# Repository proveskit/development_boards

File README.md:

# development_boards
Miscellaneous dev boards to test the components of the PROVES Kit on a smaller scale. 

## flat_sat_dev_board
This board is intended to be a "FlatSat" stand in for all of the core hardware of the PROVES Kit! By putting all of the microcontrollers, sensors, and communications hardware on one convenient board you can carry it around with you where ever you'd like!

Find a link to the documentation for that [here](https://docs.proveskit.space/en/latest/core_documentation/hardware/flatsat_dev_board/)! 

## Camera_board_v2
This board is currently being developed for the Irvington High School Girls in STEM Club team, who are looking to fly a camera on Pleiades - Orpheus. 

## Mux_driver_board_v1
This board is a breakout hosting both the TCA I2C Multiplexer and an I2C based LED driver. It is intended to be mounted as a daughter card on another PCB and used to provide access to additional protected I2C buses. 

## FC_Advanced_Carrier 
This is the initial design for a board that is able to accept an NVIDIA Jetson Nano SoM.

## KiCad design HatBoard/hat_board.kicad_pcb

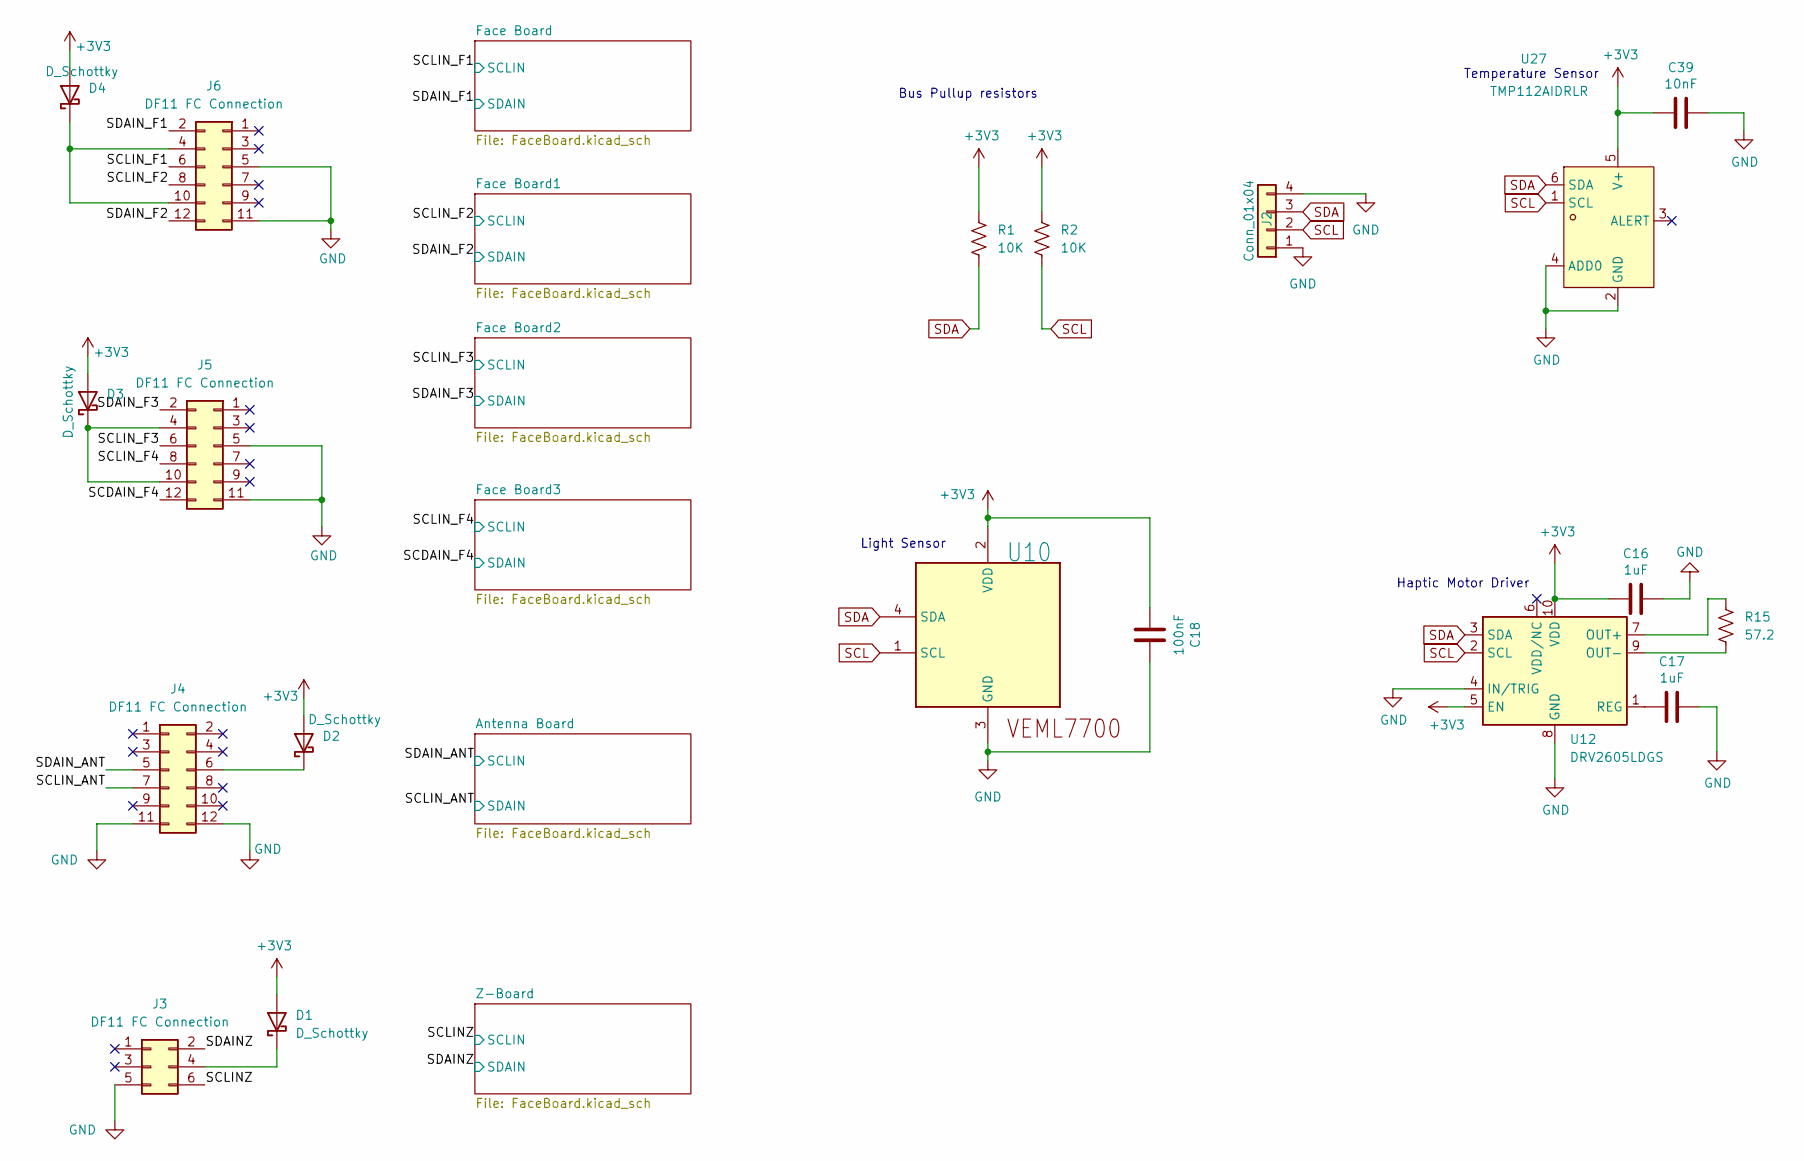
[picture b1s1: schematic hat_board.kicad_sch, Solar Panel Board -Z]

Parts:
C16, C17: 1uF; C_0805_2012Metric
C18: 100nF; C_0402_1005Metric
C39: 10nF; C_0402_1005Metric
D1, D2, D3, D4: D_Schottky; POWERDI-123_L2.8-W1.8-LS3.7-RD
J2: Conn_01x04; PinHeader_1x04_P2.00mm_Vertical
J3, J4, J5, J6: DF11 FC Connection; CONN-TH_DF11-12DS-2DSA-05
R1, R2: 10K; R_0603_1608Metric
R15: 57.2; R_0603_1608Metric
U10: VEML7700; SENSOR-SMD_EML7700-TT
U12: DRV2605LDGS; VSSOP-10_3x3mm_P0.5mm
U27: TMP112AIDRLR; SOT-563_L1.6-W1.2-P0.50-LS1.6-BR; LCSC Part C28927

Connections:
+3V3: C16.1, C18.1, C39.1, D1.2 (A), D2.2 (A), D3.2 (A), D4.2 (A), R1.2, R2.2, U10.2 (VDD), U12.5 (EN), U12.10 (VDD), U27.5 (V+); also elsewhere on the board
/SCDAIN_F4: J5.12; also elsewhere on the board
/SCLINZ: J3.6; also elsewhere on the board
/SCLIN_ANT: J4.7; also elsewhere on the board
/SCLIN_F1: J6.6; also elsewhere on the board
/SCLIN_F2: J6.8; also elsewhere on the board
/SCLIN_F3: J5.6; also elsewhere on the board
/SCLIN_F4: J5.8; also elsewhere on the board
/SDAINZ: J3.2; also elsewhere on the board
/SDAIN_ANT: J4.5; also elsewhere on the board
/SDAIN_F1: J6.2; also elsewhere on the board
/SDAIN_F2: J6.12; also elsewhere on the board
/SDAIN_F3: J5.2; also elsewhere on the board
GND: C16.2, C17.2, C18.2, C39.2, J2.1, J2.4, J3.5, J4.11, J4.12, J5.5, J5.11, J6.5, J6.11, U10.3 (GND), U12.4 (IN/TRIG), U12.8 (GND), U27.2 (GND), U27.4 (ADD0); also elsewhere on the board
unnamed: D1.1 (K), J3.4
unnamed: D2.1 (K), J4.6
unnamed: D3.1 (K), J5.4, J5.10
unnamed: D4.1 (K), J6.4, J6.10
unnamed: R15.1, U12.7 (OUT+)
unnamed: R15.2, U12.9 (OUT-)
unnamed: C17.1, U12.1 (REG)
SCL: J2.2, R2.1, U10.1 (SCL), U12.2 (SCL), U27.1 (SCL); also elsewhere on the board
SDA: J2.3, R1.1, U10.4 (SDA), U12.3 (SDA), U27.6 (SDA); also elsewhere on the board

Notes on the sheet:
Bus Pullup resistors
Temperature Sensor
Haptic Motor Driver
Light Sensor

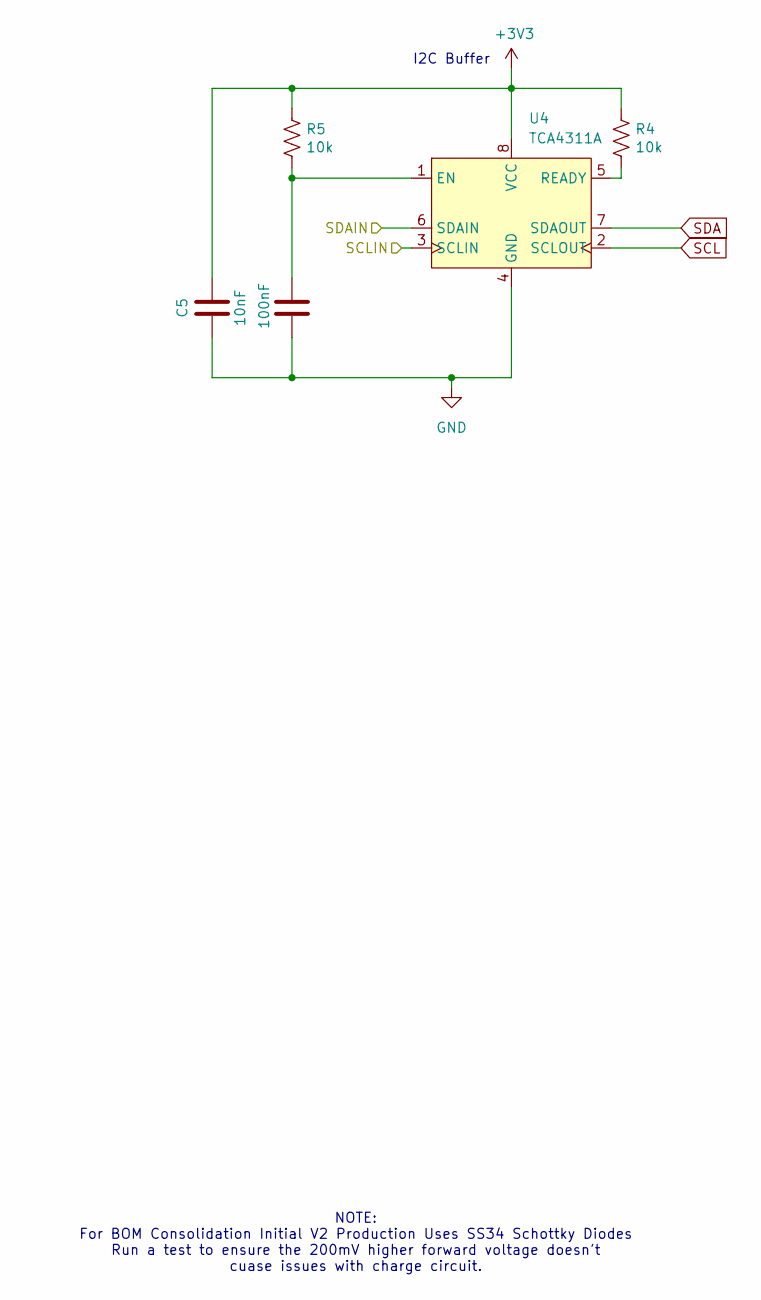
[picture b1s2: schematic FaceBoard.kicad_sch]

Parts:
C4: 100nF; C_0402_1005Metric
C5: 10nF; C_0805_2012Metric
R4, R5: 10k; R_0603_1608Metric
U4: TCA4311A; VSSOP-8_3x3mm_P0.65mm

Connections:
+3V3: C5.1, R4.1, R5.1, U4.8 (VCC); also elsewhere on the board
/SCLIN_F1: U4.3 (SCLIN); also elsewhere on the board
/SDAIN_F1: U4.6 (SDAIN); also elsewhere on the board
GND: C4.2, C5.2, U4.4 (GND); also elsewhere on the board
unnamed: C4.1, R5.2, U4.1 (EN)
unnamed: R4.2, U4.5 (READY)
SCL: U4.2 (SCLOUT); also elsewhere on the board
SDA: U4.7 (SDAOUT); also elsewhere on the board

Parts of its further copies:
C7, C13, C19, C25, C31: 10nF; C_0805_2012Metric
C8, C14, C20, C26, C32: 100nF; C_0402_1005Metric
R6, R7, R11, R12, R16, R17, R21, R22, R26, R27: 10k; R_0603_1608Metric
U5, U9, U13, U17, U21: TCA4311A; VSSOP-8_3x3mm_P0.65mm

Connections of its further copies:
+3V3: C7.1, C13.1, C19.1, C25.1, C31.1, R6.1, R7.1, R11.1, R12.1, R16.1, R17.1, R21.1, R22.1, R26.1, R27.1, U5.8 (VCC), U9.8 (VCC), U13.8 (VCC), U17.8 (VCC), U21.8 (VCC); also elsewhere on the board
/SCDAIN_F4: U13.6 (SDAIN); also elsewhere on the board
/SCLINZ: U17.3 (SCLIN); also elsewhere on the board
/SCLIN_ANT: U21.6 (SDAIN); also elsewhere on the board
/SCLIN_F2: U5.3 (SCLIN); also elsewhere on the board
/SCLIN_F3: U9.3 (SCLIN); also elsewhere on the board
/SCLIN_F4: U13.3 (SCLIN); also elsewhere on the board
/SDAINZ: U17.6 (SDAIN); also elsewhere on the board
/SDAIN_ANT: U21.3 (SCLIN); also elsewhere on the board
/SDAIN_F2: U5.6 (SDAIN); also elsewhere on the board
/SDAIN_F3: U9.6 (SDAIN); also elsewhere on the board
GND: C7.2, C8.2, C13.2, C14.2, C19.2, C20.2, C25.2, C26.2, C31.2, C32.2, U5.4 (GND), U9.4 (GND), U13.4 (GND), U17.4 (GND), U21.4 (GND); also elsewhere on the board
unnamed: C8.1, R6.2, U5.1 (EN)
unnamed: R7.2, U5.5 (READY)
unnamed: C14.1, R11.2, U9.1 (EN)
unnamed: R12.2, U9.5 (READY)
unnamed: C20.1, R16.2, U13.1 (EN)
unnamed: R17.2, U13.5 (READY)
unnamed: C26.1, R21.2, U17.1 (EN)
unnamed: R22.2, U17.5 (READY)
unnamed: C32.1, R26.2, U21.1 (EN)
unnamed: R27.2, U21.5 (READY)
SCL: U5.2 (SCLOUT), U9.2 (SCLOUT), U13.2 (SCLOUT), U17.2 (SCLOUT), U21.2 (SCLOUT); also elsewhere on the board
SDA: U5.7 (SDAOUT), U9.7 (SDAOUT), U13.7 (SDAOUT), U17.7 (SDAOUT), U21.7 (SDAOUT); also elsewhere on the board

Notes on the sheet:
NOTE: For BOM Consolidation Initial V2 Production Uses SS34 Schottky Diodes Run a test to ensure the 200mV higher forward voltage doesn't cuase issues with charge circuit.
I2C Buffer

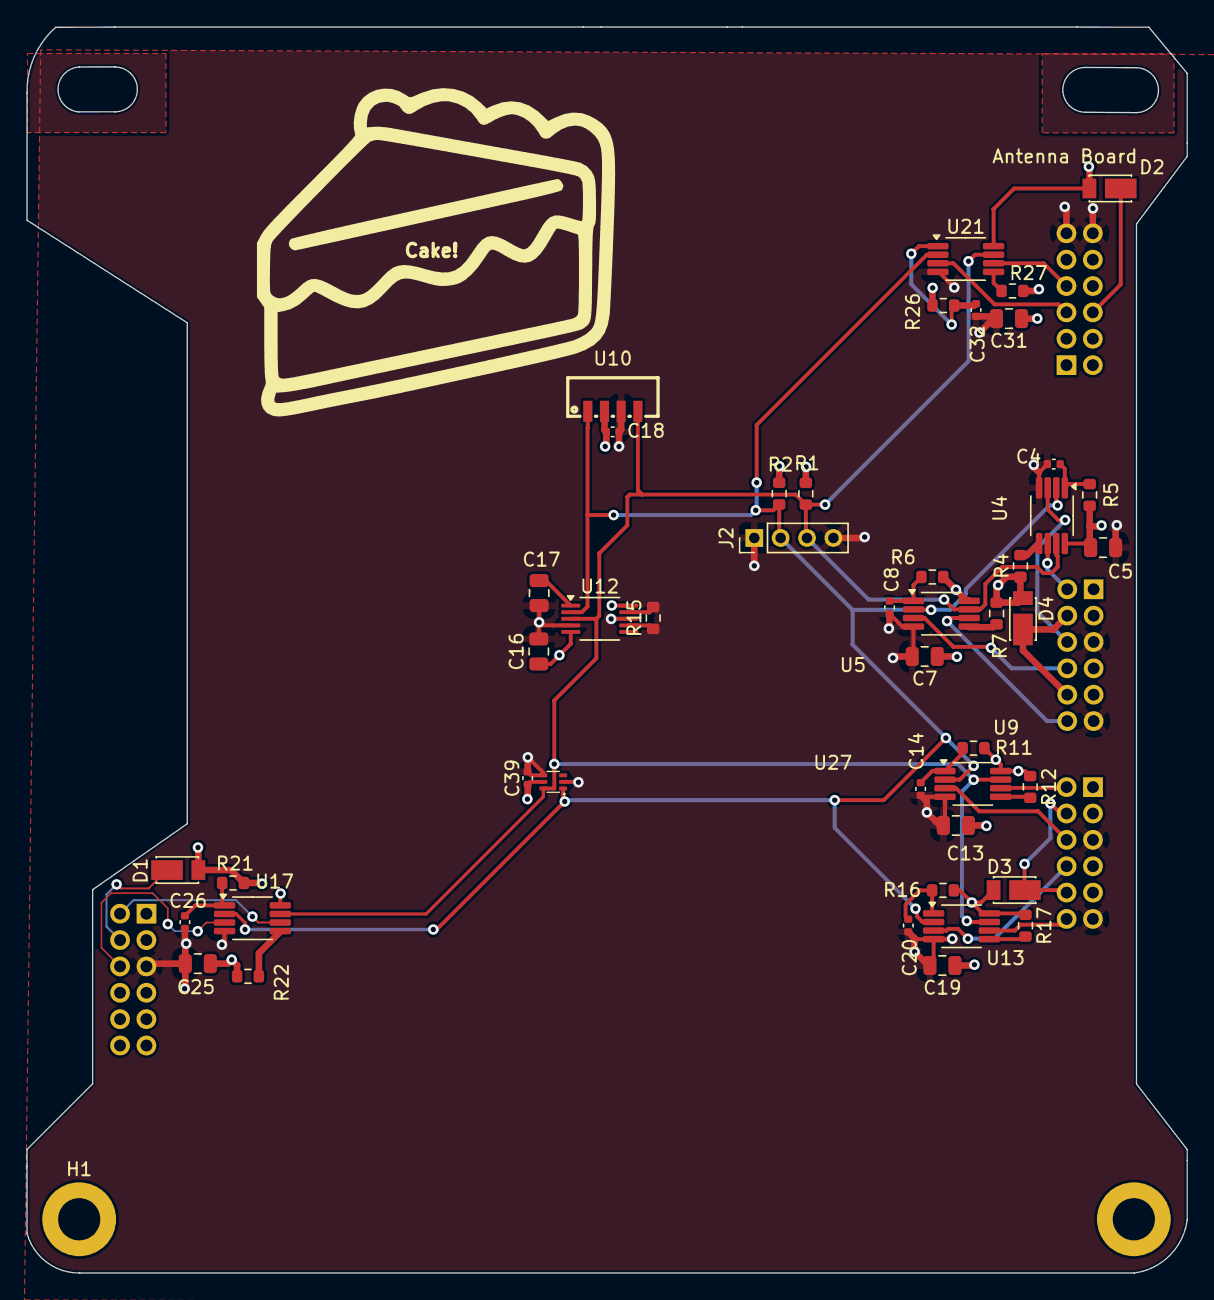
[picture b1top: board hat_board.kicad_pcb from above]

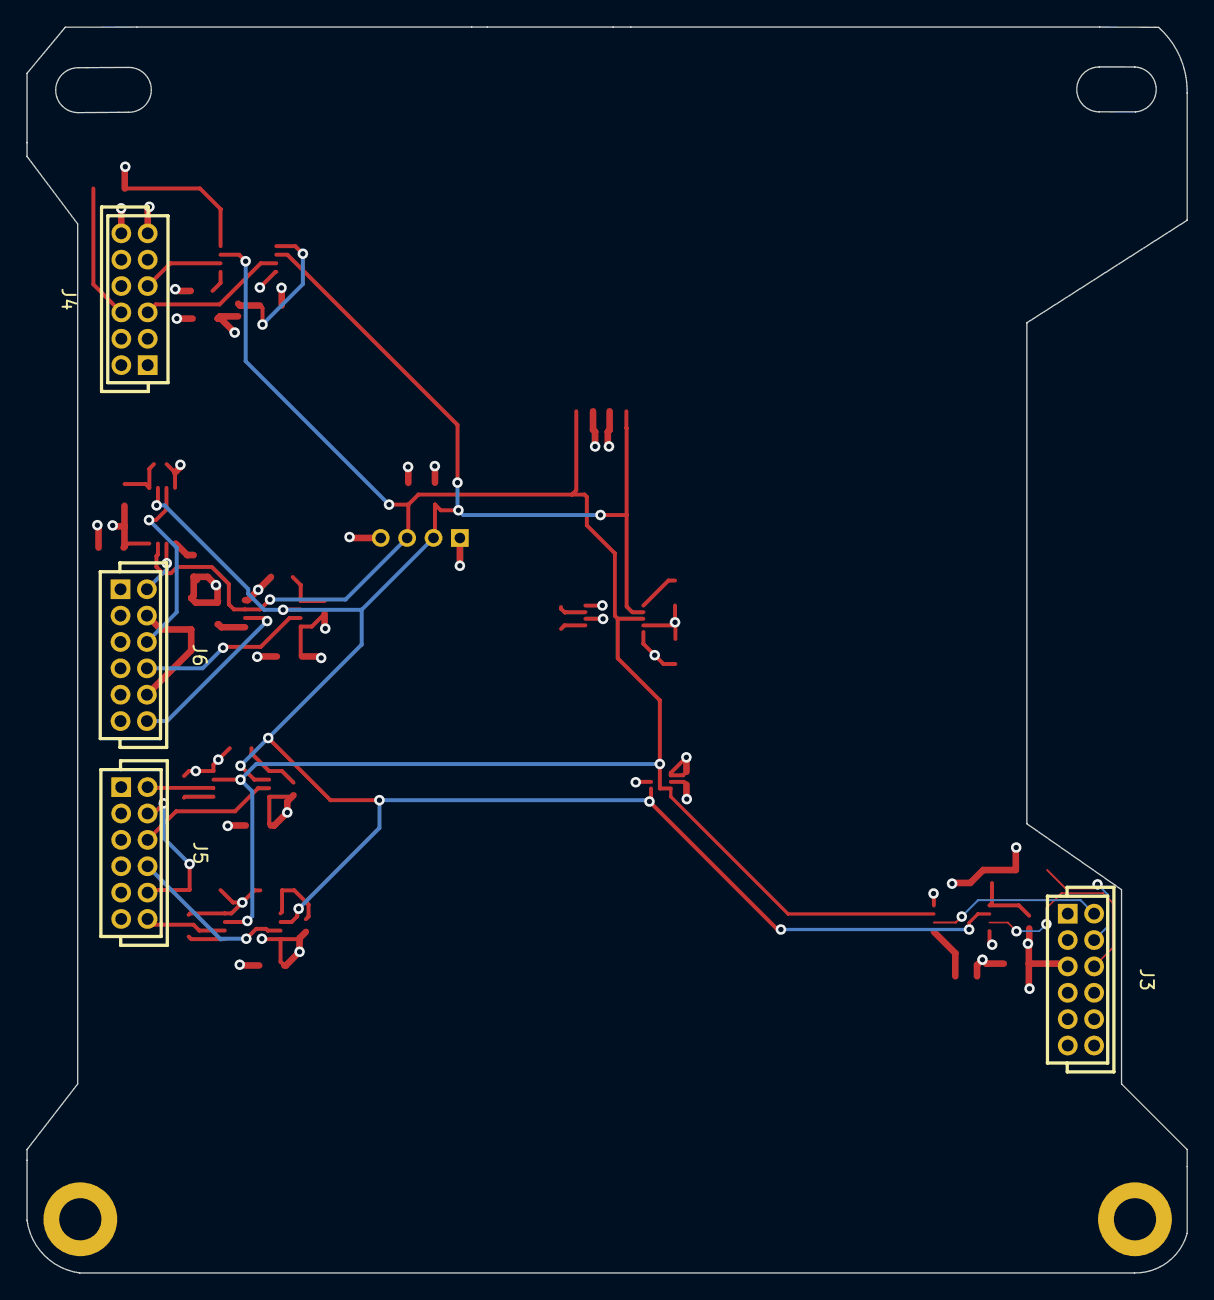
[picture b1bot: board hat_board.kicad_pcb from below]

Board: 4 copper layers, 88.0 x 94.5 mm, 52 parts (4 on the bottom side), 35 nets.

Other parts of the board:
Cake!: LOGO
H1, H2: MountingHole; MountingHole_3.2mm_M3_DIN965_Pad

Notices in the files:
parts and their libraries:
Copyright 2021 Accelerated Designs. All rights reserved.
